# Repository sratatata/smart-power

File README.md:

# Smart-Power

This project is my attempt of IoT hacking. 
Designed for switching power in RC outlet switches with use of WIFI network, including smartwatch and android phone apps. 

# Project directories

1. esp-program - sending signals over 433.92 MHz radio to RC Switches (Kemot with dip switches)
2. circuit - circuit design USB + ESP8266 + LF33CV + 433 Transmiter
3. case - files for 3d printing
4. tizen - application for Gear S watch
5. android - app for Android phone

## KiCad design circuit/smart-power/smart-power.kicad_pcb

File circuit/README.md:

TBD

# Schematic

# Assembly
Placement:

Done circuit on stripboard. 

# Parts:

* ESP8266-01 - wifi module and micro controller
* LF33CV - 3.3 voltage regulator
* 2.2uF Electrolitic Capacitor
* 0.1uF Ceramic Capacitor
* Goldpin male socket 02x4
* 2 x 12mm Pushbuttons
* USB typa A plug - for PCB
* [WRL-10534](https://www.sparkfun.com/products/10534) - 433 rc transmitter
* Strip Board

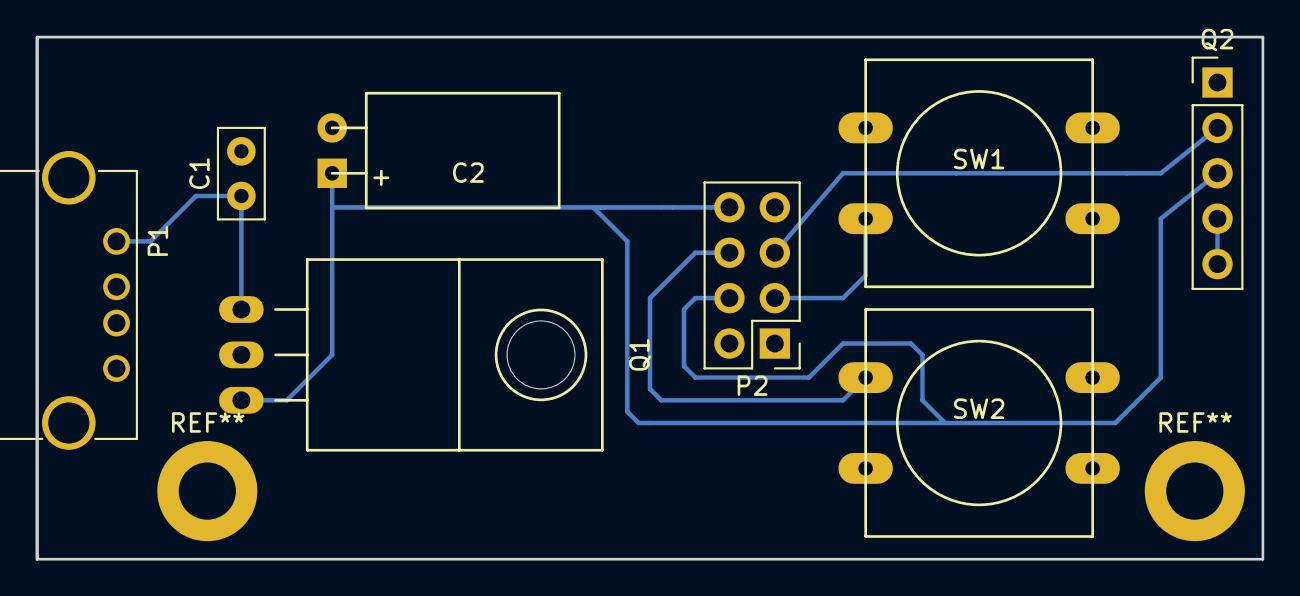
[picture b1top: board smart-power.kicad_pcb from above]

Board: 2 copper layers, 68.6 x 29.2 mm, 8 parts (0 on the bottom side), 7 nets.

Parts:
C1: C_Small; C_Disc_D5.0mm_W2.5mm_P2.50mm
C2: CP_Small; C1V7H
P1: USB_A
P2: ESP-8266-01; Pin_Header_Straight_2x04_Pitch2.54mm
Q1: LF33CV; TO-220_Neutral123_Horizontal
Q2: 433-module; Pin_Header_Straight_1x05_Pitch2.54mm
SW1: SW_RESET; SW_PUSH-12mm
SW2: RST; SW_PUSH-12mm

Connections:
+5V: C1.1, P1.1, Q1.1
Antena: Q2.4, Q2.5
GND: C1.2, C2.2, P1.4, P2.1, Q1.2, Q2.1, SW1.1, SW2.2
unnamed: C2.1, P2.4, P2.8, Q1.3, Q2.3
unnamed: P2.3, SW1.2
unnamed: P2.5, Q2.2
unnamed: P2.6, SW2.1

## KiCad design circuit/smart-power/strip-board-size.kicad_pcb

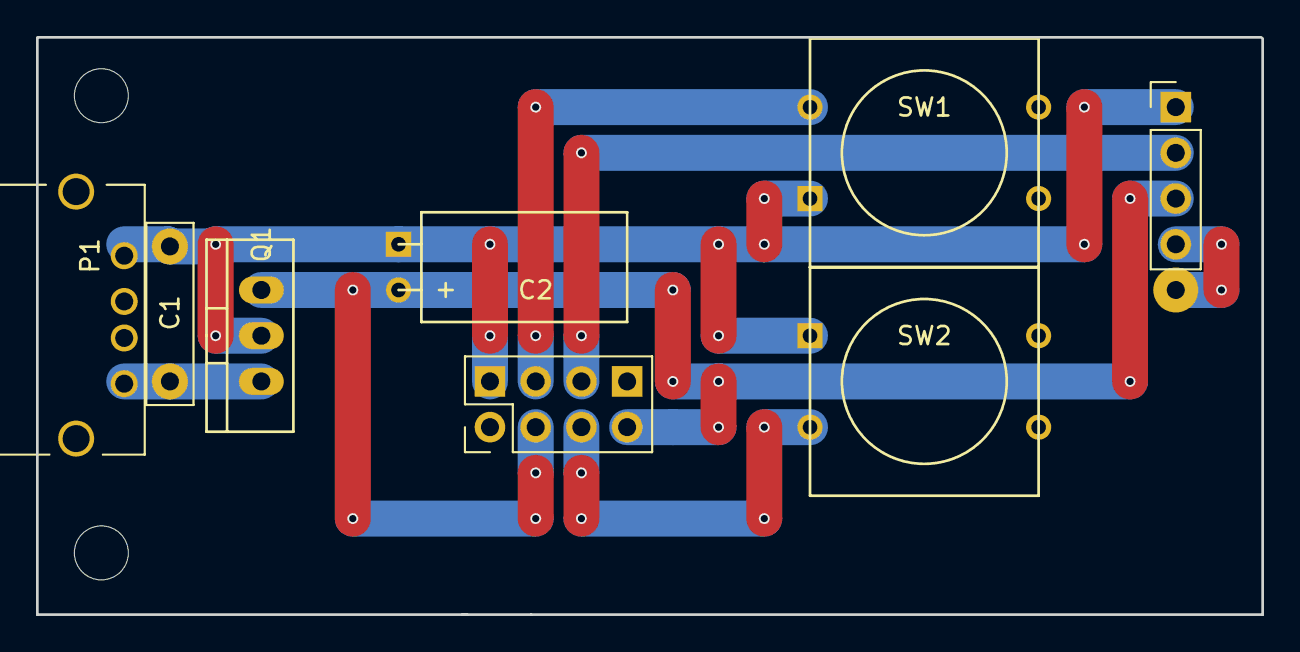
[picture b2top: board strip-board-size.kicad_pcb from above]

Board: 2 copper layers, 68.1 x 32.1 mm, 8 parts (0 on the bottom side), 6 nets.

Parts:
C1: 0.1uF; C_Rect_L10.0mm_W2.5mm_P7.50mm_MKS4
C2: 2,2uF; C1V5H
P1: USB_A
P2: ESP-8266-01; Pin_Header_Straight_2x04_Pitch2.54mm
Q1: LF33CV; TO-220_Neutral123_Vertical
Q2: 433-module; Pin_Header_Straight_1x04_Pitch2.54mm
SW1: SW_RESET; SW_PUSH-12mm
SW2: RST; SW_PUSH-12mm

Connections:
+5V: C1.1, P1.1, Q1.1
GND: C1.2, C2.2, P1.4, P2.2, Q1.2, Q2.1, SW1.1, SW2.2
unnamed: C2.1, P2.CH_P, P2.VCC, Q1.3, Q2.VCC
unnamed: P2.G2, SW1.2
unnamed: P2.G0, Q2.DATA
unnamed: P2.RST, SW2.1

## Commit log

2016-12-29 Init commit
2016-12-29 Add wifi manager support wifi reset on GPIO2 FALLING state
2016-12-29 Add 433.92 RC transmiter support
2016-12-29 Add usage section to readme.md
2016-12-30 Add minimum working version
2016-12-31 Add circuit on stripboard photo
2017-01-04 Move logic to core package
2017-01-06 Refactoring of RemoteAdapter and HttpExecutor
2017-01-06 Files storage added
2017-01-07 Add floating action button
2017-01-07 Added user prompt
2017-01-08 Added ip settings
2017-01-08 Added swipe ListView and delete action
2017-01-08 Fix convert view issue during item removal
2017-01-16 Add tizen simple webapp
2017-01-18 Bigger UI elements
2017-01-29 Add new look and fill + adding devices popup
2017-01-29 Add new icon
2017-01-29 Add remove buttons popup
2017-02-14 Add circuit design files
